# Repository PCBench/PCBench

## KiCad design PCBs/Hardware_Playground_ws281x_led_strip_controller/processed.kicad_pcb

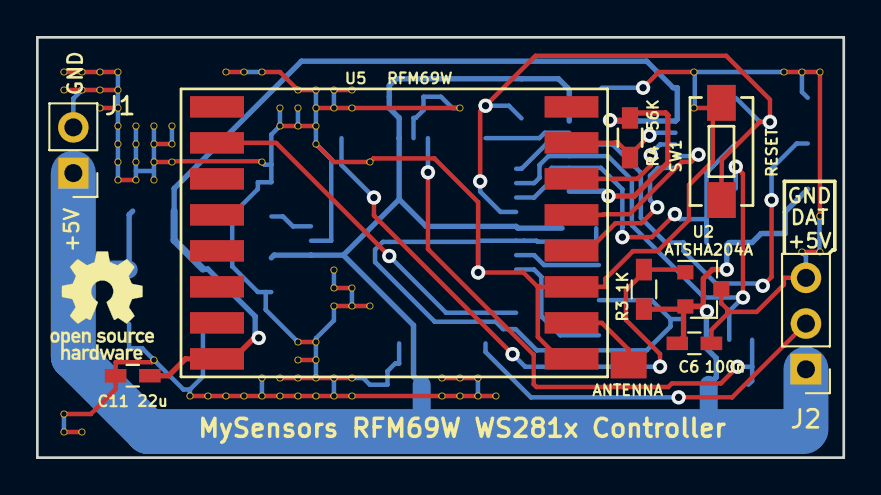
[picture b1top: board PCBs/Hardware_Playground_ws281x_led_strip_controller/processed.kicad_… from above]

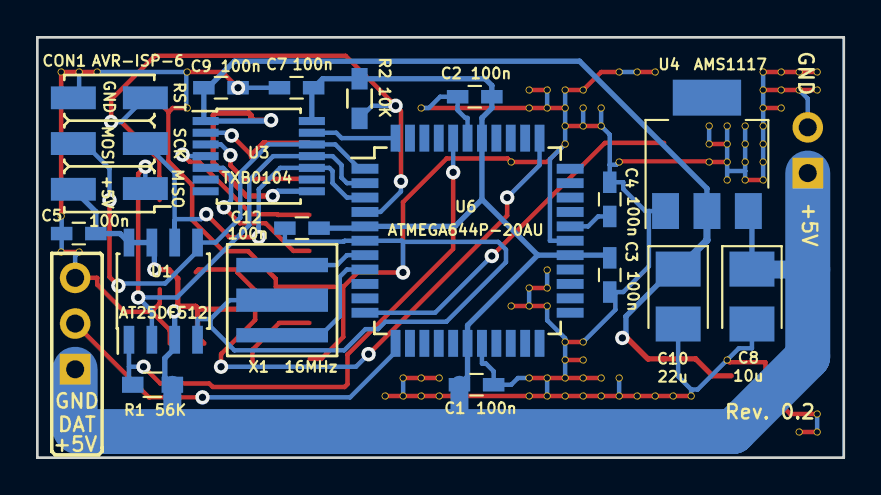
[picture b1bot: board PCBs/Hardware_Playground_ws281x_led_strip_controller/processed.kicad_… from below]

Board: 2 copper layers, 44.8 x 23.4 mm, 117 parts (18 on the bottom side), 20 nets.

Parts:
C1, C2, C3, C4, C5, C6, C7, C9, C12: 100n; C_0603_HandSoldering
C8: 10u; CP_Tantalum_Case-B_EIA-3528-21_Reflow
C10: 22u; CP_Tantalum_Case-B_EIA-3528-21_Reflow
C11: 22u; C_0603_HandSoldering
CON1: AVR-ISP-6; AVR_ISP_SMT_Small_02x03
J1: PWR; Pin_Header_Straight_1x02_Pitch2.54mm
J2: CTRL_OUT; Pin_Header_Straight_1x03_Pitch2.54mm
P1: ANTENNA; 1pin_smd_2mm
R1, R4: 56K; R_0603_HandSoldering
R2: 10K; R_0603_HandSoldering
R3: 1K; R_0603_HandSoldering
SW1: RESET; SW_SPST_EVQPE1
U1: AT25DF512; SOIC-8_3.9x4.9mm_Pitch1.27mm
U2: ATSHA204A; SOT-23
U3: TXB0104; TSSOP-14_4.4x5mm_Pitch0.65mm
U4: AMS1117; SOT-223
U5: RFM69W; RFM69HW_SMD_Handsoldering
U6: ATMEGA644P-20AU; TQFP-44_10x10mm_Pitch0.8mm
V10_2, V10_3, V10_21, V10_22, V11_2, V11_3, V11_22, V12_2, V12_3, V12_4, V13_2, V13_3, V13_4, V13_5, V13_6, V13_7, V13_8, V14_5, V14_6, V14_7, V14_8, V15_5, V15_6, V15_7, V15_8, V15_18, V16_5, V16_6, V16_7, V17_20, V18_20, V19_2, V19_20, V20_2, V20_20, V21_2, V21_7, V21_19, V21_20, V22_4, V22_5, V22_19, V22_20, V23_3, V23_4, V23_5, V23_17, V23_18, V23_19, V23_20, V24_3, V24_4, V24_5, V24_6, V24_17, V24_18, V24_19, V24_20, V25_3, V25_4, V25_13, V25_14, V25_15, V25_19, V25_20, V26_3, V26_4, V26_14, V26_15, V26_19, V26_20, V27_7, V27_15, V31_19, V31_20, V32_4, V32_19, V32_20, V33_19, V33_20, V34_20, V45_2, V45_4, V50_2, V51_2, V51_12, V52_2, V52_10, V52_12: AUTO_VIA; VIA_MATRIX
X1: 16MHz; ZTTCS-3

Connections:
+3V3: C9.2, C10.1, C11.1, R4.2, U3.1, U3.8, U4.2, U5.8
+5V: C1.2, C2.2, C3.2, C5.1, C6.1, C7.1, C8.1, C12.2, CON1.2, J1.1, J2.1, R1.2, R2.1, R3.2, U1.3, U1.7, U1.8, U2.2, U3.14, U4.3, U6.5, U6.17, U6.27, U6.38
/ATSHA204A: R3.1, U2.1, U6.34
/D_OUT: J2.2, U6.12
/MISO: CON1.1, U1.2, U3.11, U6.2
/MOSI: CON1.4, U1.5, U3.12, U6.1
/RFM69W_INT: U5.2, U6.11
/RFM69W_SS: U3.13, U6.44
/RST: CON1.5, R2.2, SW1.1, U6.4
/SCK: CON1.3, U1.6, U3.10, U6.3
/SPI_FLASH_SS: R1.1, U1.1, U6.40
GND: C1.1, C2.1, C3.1, C4.1, C5.2, C6.2, C7.2, C8.2, C9.1, C10.2, C11.2, C12.1, CON1.6, J1.2, J2.3, SW1.2, U1.4, U2.3, U4.1, U5.9, U5.11, U6.6, U6.18, U6.28, U6.39, V10_2.1, V10_3.1, V10_21.1, V10_22.1, V11_2.1, V11_3.1, V11_22.1, V12_2.1, V12_3.1, V12_4.1, V13_2.1, V13_3.1, V13_4.1, V13_5.1, V13_6.1, V13_7.1, V13_8.1, V14_5.1, V14_6.1, V14_7.1, V14_8.1, V15_5.1, V15_6.1, V15_7.1, V15_8.1, V15_18.1, V16_5.1, V16_6.1, V16_7.1, V17_20.1, V18_20.1, V19_2.1, V19_20.1, V20_2.1, V20_20.1, V21_2.1, V21_7.1, V21_19.1, V21_20.1, V22_4.1, V22_5.1, V22_19.1, V22_20.1, V23_3.1, V23_4.1, V23_5.1, V23_17.1, V23_18.1, V23_19.1, V23_20.1, V24_3.1, V24_4.1, V24_5.1, V24_6.1, V24_17.1, V24_18.1, V24_19.1, V24_20.1, V25_3.1, V25_4.1, V25_13.1, V25_14.1, V25_15.1, V25_19.1, V25_20.1, V26_3.1, V26_4.1, V26_14.1, V26_15.1, V26_19.1, V26_20.1, V27_7.1, V27_15.1, V31_19.1, V31_20.1, V32_4.1, V32_19.1, V32_20.1, V33_19.1, V33_20.1, V34_20.1, V45_2.1, V45_4.1, V50_2.1, V51_2.1, V51_12.1, V52_2.1, V52_10.1, V52_12.1, X1.2
unnamed: C4.2, U6.29
unnamed: P1.1, U5.10
unnamed: R4.1, U3.2, U5.15
unnamed: U3.3, U5.14
unnamed: U3.4, U5.13
unnamed: U3.5, U5.12
unnamed: U6.7, X1.1
unnamed: U6.8, X1.3

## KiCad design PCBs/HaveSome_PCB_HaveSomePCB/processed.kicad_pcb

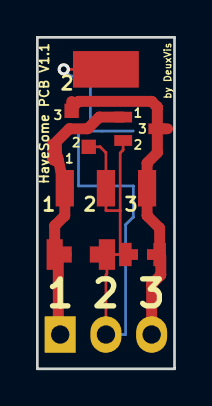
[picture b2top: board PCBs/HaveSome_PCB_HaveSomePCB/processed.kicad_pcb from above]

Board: 2 copper layers, 7.6 x 18.4 mm, 8 parts (0 on the bottom side), 3 nets.

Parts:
PINS1: CONN_01X03; Pin_Header_Straight_1x03
SMD402: R0402; R_0402
SMD603: R0603; R_0603
SMD805: R0805; R_0805
SMD1206: R1206; R_1206
SOT23: APE8865NL-33-HF-3; SOT-23
SOT223: LD1117S33CTR; SOT-223
SOT323: BFR92; SOT-323

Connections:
unnamed: PINS1.1, SMD603.2, SMD1206.2, SOT23.1, SOT223.1, SOT323.1
unnamed: PINS1.2, SMD402.2, SMD603.1, SMD805.2, SMD1206.1, SOT23.2, SOT223.2, SOT223.4, SOT323.2
unnamed: PINS1.3, SMD402.1, SMD805.1, SOT23.3, SOT223.3, SOT323.3

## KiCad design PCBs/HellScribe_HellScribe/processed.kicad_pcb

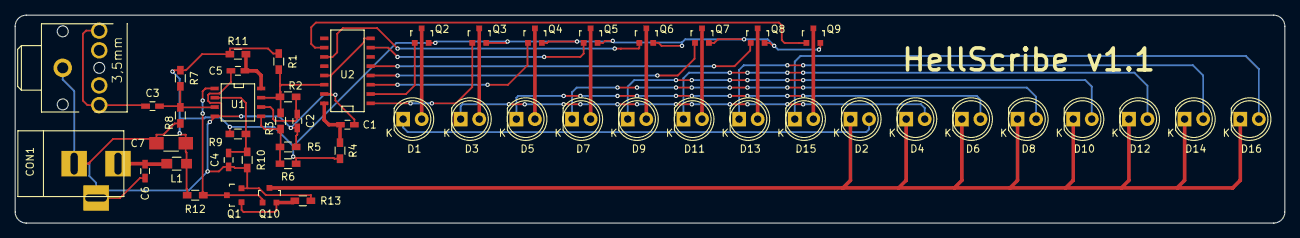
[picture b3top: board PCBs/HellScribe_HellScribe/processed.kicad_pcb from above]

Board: 2 copper layers, 173.7 x 28.4 mm, 51 parts (0 on the bottom side), 38 nets.

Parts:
C1, C3, C4, C5, C6: 0.1uF; C_0603_HandSoldering
C2: 2.2nF; C_0603_HandSoldering
C7: 10uF; R_1206_HandSoldering
CON1: +12v; BARREL_JACK
D1, D2, D3, D4, D5, D6, D7, D8, D9, D10, D11, D12, D13, D14, D15, D16: LED; LED-5MM
J1: STX-3100-5N; STX3100
L1: 10uH; R_0805_HandSoldering
Q1, Q10: 2N3904; SOT-23
Q2, Q3, Q4, Q5, Q6, Q7, Q8, Q9: FDV304P; SOT-23
R1: 1k; R_0603_HandSoldering
R2: 2.4M; R_0603_HandSoldering
R3, R5, R6, R7, R8, R9: 10k; R_0603_HandSoldering
R4, R11: 100; R_0603_HandSoldering
R10: 11k; R_0603_HandSoldering
R12: 2.2k; R_0603_HandSoldering
R13: 10; R_0603_HandSoldering
U1: LM393; SOIC-8-N
U2: CD4022; SO-16-N

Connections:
+12V: C7.2, L1.1, Q2.2, Q3.2, Q4.2, Q5.2, Q6.2, Q7.2, Q8.2, Q9.2, R1.1, R4.1, R6.2, R7.1, R9.2, R11.1, R12.2
GND: C1.2, C2.1, C4.1, C5.1, C6.1, C7.1, CON1.2, CON1.3, J1.1, Q1.2, R5.1, R8.2, R10.2, R13.2, U1.4, U2.8, U2.13, U2.15
unnamed: C2.2, R2.2, U1.6
unnamed: C3.1, R7.2, R8.1, U1.3
unnamed: C3.2, J1.2, J1.5
unnamed: C4.2, R9.1, R10.1, U1.2
unnamed: C5.2, R11.2, U1.8
unnamed: C6.2, CON1.1, L1.2
unnamed: D1.1, D2.2
unnamed: D1.2, Q2.3
unnamed: D3.1, D4.2
unnamed: D3.2, Q3.3
unnamed: D5.1, D6.2
unnamed: D5.2, Q4.3
unnamed: D7.1, D8.2
unnamed: D7.2, Q5.3
unnamed: D9.2, Q6.3
unnamed: D2.1, D4.1, D6.1, D8.1, D10.1, D12.1, D14.1, D16.1, Q10.3
unnamed: D9.1, D10.2
unnamed: D11.1, D12.2
unnamed: D11.2, Q7.3
unnamed: D13.1, D14.2
unnamed: D13.2, Q8.3
unnamed: D15.1, D16.2
unnamed: D15.2, Q9.3
unnamed: Q1.1, Q10.2, R13.1
unnamed: Q1.3, Q10.1, R12.1, U1.1
unnamed: Q2.1, U2.2
unnamed: Q3.1, U2.1
unnamed: Q4.1, U2.3
unnamed: Q5.1, U2.7
unnamed: Q6.1, U2.11
unnamed: Q7.1, U2.4
unnamed: Q8.1, U2.5
unnamed: Q9.1, U2.10
unnamed: R1.2, R2.1, R3.2, U1.7, U2.14
unnamed: R3.1, R5.2, R6.1, U1.5
VDD: C1.1, R4.2, U2.16

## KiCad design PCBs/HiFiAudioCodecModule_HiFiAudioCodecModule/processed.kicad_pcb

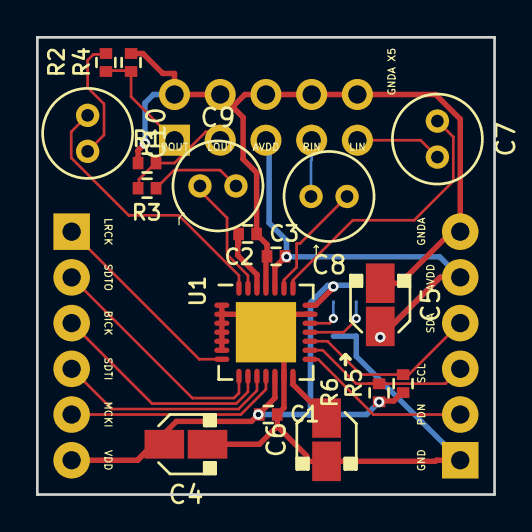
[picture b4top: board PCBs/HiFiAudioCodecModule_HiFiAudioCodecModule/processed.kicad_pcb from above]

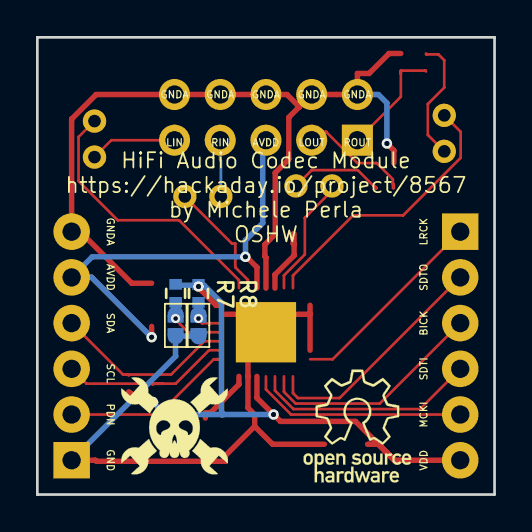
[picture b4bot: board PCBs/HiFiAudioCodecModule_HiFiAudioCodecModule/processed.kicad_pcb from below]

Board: 2 copper layers, 25.4 x 25.4 mm, 26 parts (6 on the bottom side), 26 nets.

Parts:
C1, C2: 0.1u; C_0402
C3: 1u; C_0402
C4, C5: 10u; CAP_ELEC_SMD_3x5mm
C6: 1u; CAP_ELEC_SMD_3x5mm
C7, C8: 10u; C_Radial_D5_L11_P2-bipolar
C9, C10: 1u; C_Radial_D5_L11_P2-bipolar
JP1, JP2: Jumper_NO_Small; SMD_Jumper
LOGO1: OSHW; LOGO
LOGO2: HACKADAY; LOGO
P1, P2: CONN_01X06; Pin_Header_Straight_1x06
P3: CONN_02X05; Pin_Header_Straight_2x05
R1, R2: 220; R_0402
R3, R4: 20K; R_0402
R5, R6, R7, R8: 1K; R_0402
U1: AK4558EN; QFN-28-2xEP_5x5mm_Pitch0.5mm

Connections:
AVDD: C2.1, C5.1, P2.5, P3.5, U1.24
BICK: P1.3, U1.9
CAD0: JP1.1, R7.2, U1.18
CAD1: JP2.1, R8.2, U1.19
GND: C1.2, C4.2, C6.2, JP1.2, JP2.2, P2.1, U1.1, U1.2, U1.3, U1.4, U1.5, U1.6, U1.13, U1.20, U1.29
GNDA: C2.2, C3.2, C5.2, P2.6, P3.2, P3.4, P3.6, P3.8, P3.10, R3.2, R4.2, U1.25
LIN: C7.1, U1.22
LIN-CON: C7.2, P3.9
LOUT: C9.1, U1.27
LOUT-CON: P3.3, R1.1, R3.1
LRCK: P1.1, U1.7
MCKI: P1.5, U1.11
unnamed: C9.2, R1.2
unnamed: C10.2, R2.2
PDN: P2.2, U1.15
RIN: C8.1, U1.23
RIN-CON: C8.2, P3.7
ROUT: C10.1, U1.28
ROUT-CON: P3.1, R2.1, R4.1
SCL: P2.3, R6.2, U1.16
SDA: P2.4, R5.2, U1.17
SDTI: P1.4, U1.10
SDTO: P1.2, U1.8
VCOM: C3.1, U1.26
VDD: C1.1, C4.1, P1.6, R5.1, R6.1, R7.1, R8.1, U1.12, U1.21
VDD18: C6.1, U1.14

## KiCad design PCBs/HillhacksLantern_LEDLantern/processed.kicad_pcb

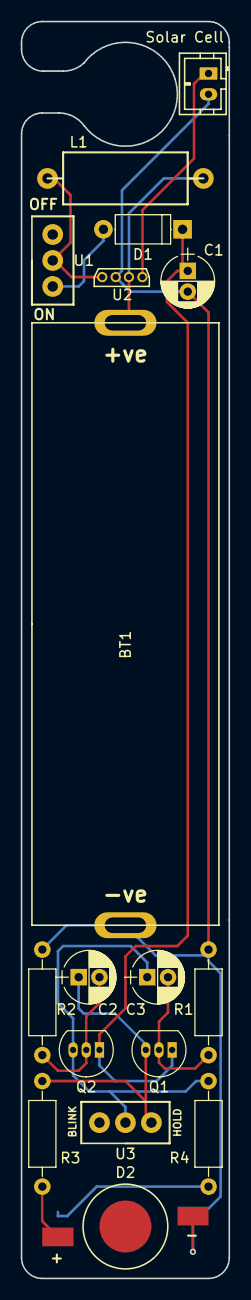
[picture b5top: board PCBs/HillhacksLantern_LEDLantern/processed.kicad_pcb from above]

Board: 2 copper layers, 20.0 x 121.0 mm, 18 parts (1 on the bottom side), 12 nets.

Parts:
BT1: Battery_Cell; BatteryHolder
C1, C2, C3: CP; CP_Radial_D5.0mm_P2.00mm
D1: D; D_A-405_P7.62mm_Horizontal
D2, D3: LED; 1W-LED
L1: L; Inductor
Q1, Q2: Q_PNP_EBC; TO-92_Inline_Narrow_Oval
R1, R2, R3, R4: R; R_Axial_DIN0207_L6.3mm_D2.5mm_P10.16mm_Horizontal
Solar Cell: Solar_Cell; JST_PH_B2B-PH-K_02x2.00mm_Straight
U1, U3: switch_on_off; Switch
U2: qf5252; YX8018

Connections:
/GND: BT1.2, C1.2, D2.1, D3.1, R1.2, R2.2, Solar Cell.2, U2.3
/VCC: C1.1, D1.1, Q1.1, Q2.1
unnamed: BT1.1, L1.2, U2.2
unnamed: C2.1, Q1.3, R3.1, U3.1
unnamed: C2.2, Q2.2, R2.1
unnamed: C3.1, Q2.3, R4.1, U3.2
unnamed: C3.2, Q1.2, R1.1
unnamed: D1.2, U1.1
unnamed: D2.2, R3.2
unnamed: D3.2, R4.2
unnamed: L1.1, U1.2, U2.4
unnamed: Solar Cell.1, U2.1

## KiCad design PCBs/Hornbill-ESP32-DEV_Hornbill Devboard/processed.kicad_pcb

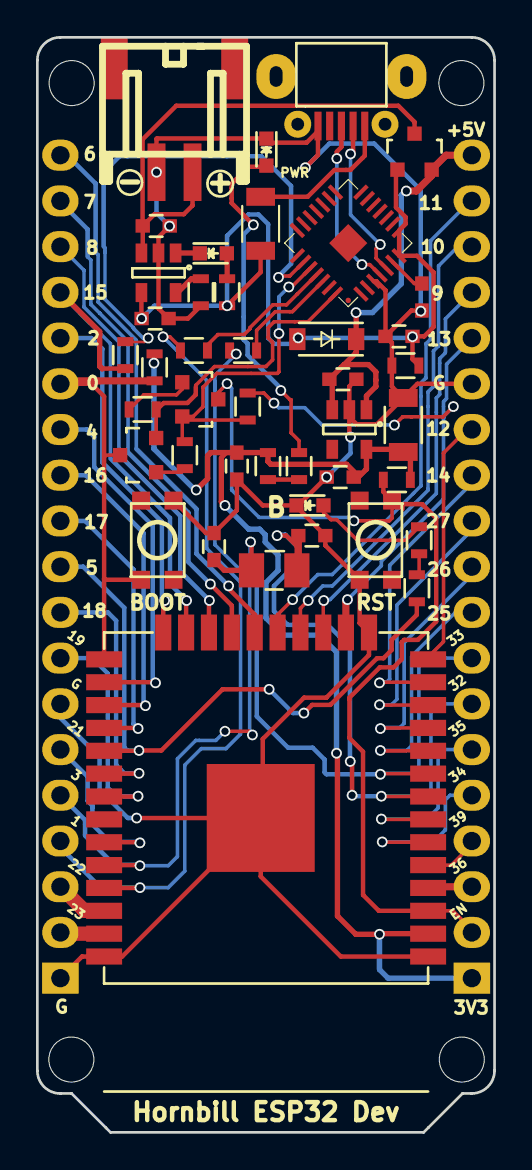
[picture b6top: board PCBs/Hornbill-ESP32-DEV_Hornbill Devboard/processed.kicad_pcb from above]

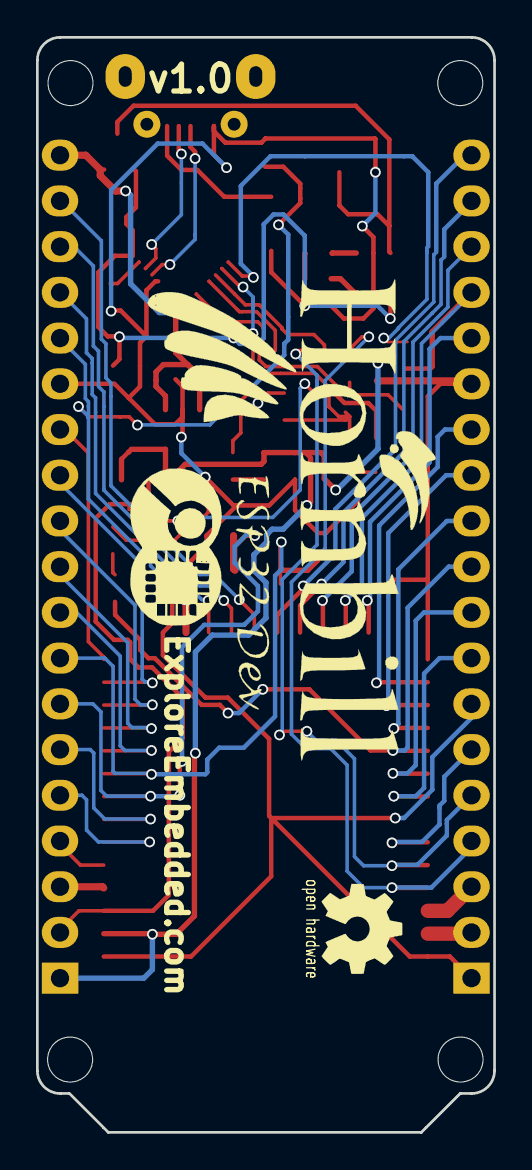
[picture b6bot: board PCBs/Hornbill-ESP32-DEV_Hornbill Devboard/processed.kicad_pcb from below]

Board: 2 copper layers, 25.4 x 60.8 mm, 51 parts (3 on the bottom side), 56 nets.

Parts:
C1, C6: 4.7uF; C_0603
C2: 1uF; C_0603
C3, C4: 0.1uF; C_0603
C5: 2.2uF; C_0603
C7: 100uF; C_1206
C8, C10: 15pF; C_0603
C9: 100nF; C_0603
CON1: USB-MINI-B; USB_Micro-B_SMD_NEW_1
D1: BAT20J; SOD-80_diode
D2: Yellow; LED-0603
D3: LED; LED-0603
D4: Blue; LED-0603
F1: 500mA; Fuse_500mA
IC1: MCP73831; SOT-23-5
M1: ESP-WROOM-32; ESP-32S
P1: LIPO; JST_SMD
P2, P3: CONN_01X19; Pin_Header_Straight_1x19
Q1: IRLML5203; SOT-23
Q2, Q3: S8050; SOT-23
R1: 100K; R_0603
R2: 2K; R_0603
R3, R4: 1K; R_0603
R5, R6: 12K; R_0603
R7, R11: 10K; R_0603
R8, R9, R10, R12, R16, R17: 0E; R_0603
R13: 330E; R_0603
SW1, SW2: SW_PUSH; smd_push2_New
U1: OSH_Symbol; Logo_silk_OSHW_6x6mm
U2: EE_Logo; Hornbill_ESP32_Dev
U3: EE_Logo; Logo_8
U4: AP2112K; SOT-23-5
U5: CP2102; cp2102_xl2
U6, U7, U8, U9: MountingHole; MountingHole_2-5mm
Y1: 32.768KHz RTC Crystal; SMD_RTC_Crstl

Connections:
+3V3: C5.1, C7.1, C9.1, M1.2, P2.1, R7.1, R11.1, R17.2, U4.5
+5V: C2.1, D1.1, P2.19, Q1.2, U4.1, U4.3
+BATT: C1.1, IC1.3, P1.1, Q1.3
/CLK: M1.20, P3.19
/CMD: M1.19, P2.18
/DTR: Q3.2, R5.2, U5.28
/EN: M1.3, P2.2, Q2.3, R7.2, SW1.1
/IO0: M1.25, P3.14, Q3.3, R11.2, SW2.1
/IO2: M1.24, P3.15
/IO4: M1.26, P3.13
/IO5: M1.29, P3.10, R16.1
/IO12: M1.14, P2.13
/IO13: M1.16, P2.15, R10.1
/IO14: M1.13, P2.12
/IO15: M1.23, P3.16, R12.1
/IO16: M1.27, P3.12
/IO17: M1.28, P3.11
/IO18: M1.30, P3.9
/IO19: M1.31, P3.8
/IO21: M1.33, P3.6
/IO22: M1.36, P3.3
/IO23: M1.37, P3.2
/IO25: M1.10, P2.9
/IO26: M1.11, P2.10
/IO27: M1.12, P2.11
/IO32: C8.1, M1.8, P2.7, Y1.1
/IO33: C10.1, M1.9, P2.8, Y1.2
/IO34: M1.6, P2.5
/IO35: M1.7, P2.6
/RTS: Q2.2, R6.2, R10.2, U5.24
/RXD0: M1.34, P3.5, R8.1
/SD0: M1.21, P3.18
/SD1: M1.22, P3.17
/SD2: M1.17, P2.16
/SD3: M1.18, P2.17
/SENSOR_VN: M1.5, P2.4
/SENSOR_VP: M1.4, P2.3
/TXD0: M1.35, P3.4, R9.1
GND: C1.2, C2.2, C3.1, C4.1, C5.2, C6.2, C7.2, C8.2, C9.2, C10.2, CON1.5, D3.1, D4.1, IC1.2, M1.1, M1.15, M1.38, P1.2, P2.14, P3.1, P3.7, R1.2, R2.2, SW1.2, SW2.2, U4.2, U5.3
unnamed: C4.2, U5.6
unnamed: CON1.1, F1.2
unnamed: CON1.2, U5.5
unnamed: CON1.3, U5.4
unnamed: D2.1, IC1.1
unnamed: D2.2, R4.2
unnamed: D3.2, R3.1
unnamed: D4.2, R13.1
unnamed: IC1.5, R2.1
unnamed: Q2.1, R5.1
unnamed: Q3.1, R6.1
unnamed: R8.2, U5.26
unnamed: R9.2, U5.25
unnamed: R12.2, U5.23
unnamed: R13.2, R16.2
unnamed: R3.2, R17.1
VCC: C3.2, C6.1, D1.2, F1.1, IC1.4, Q1.1, R1.1, R4.1, U5.7, U5.8

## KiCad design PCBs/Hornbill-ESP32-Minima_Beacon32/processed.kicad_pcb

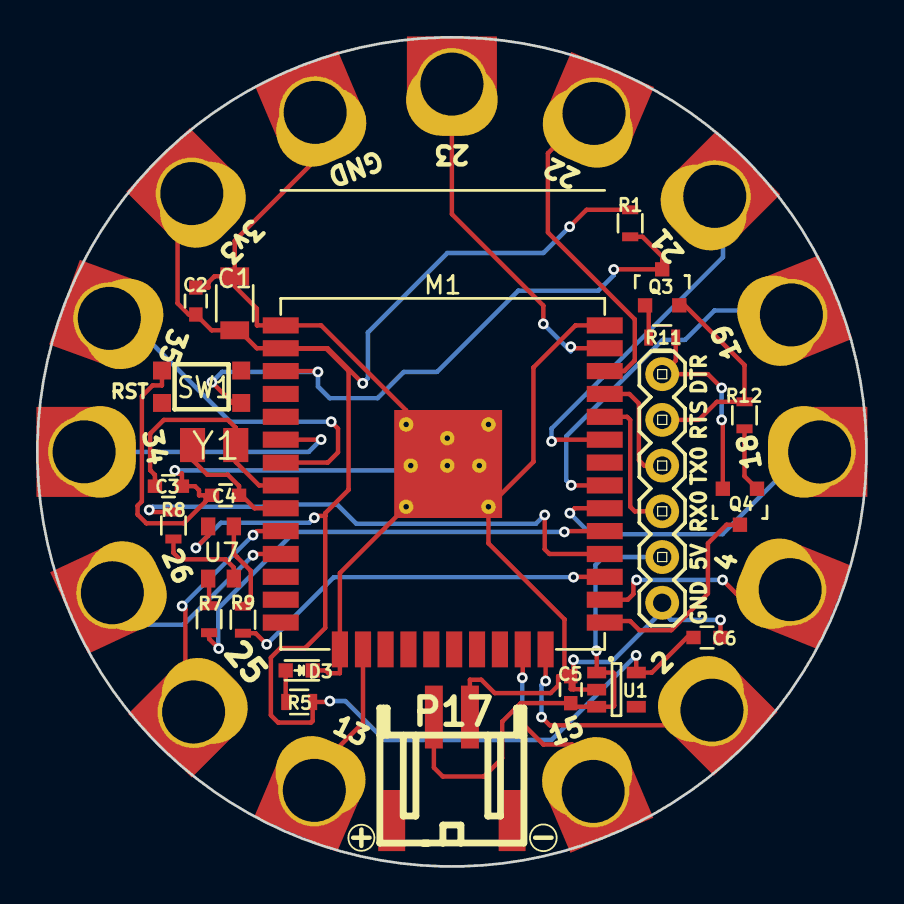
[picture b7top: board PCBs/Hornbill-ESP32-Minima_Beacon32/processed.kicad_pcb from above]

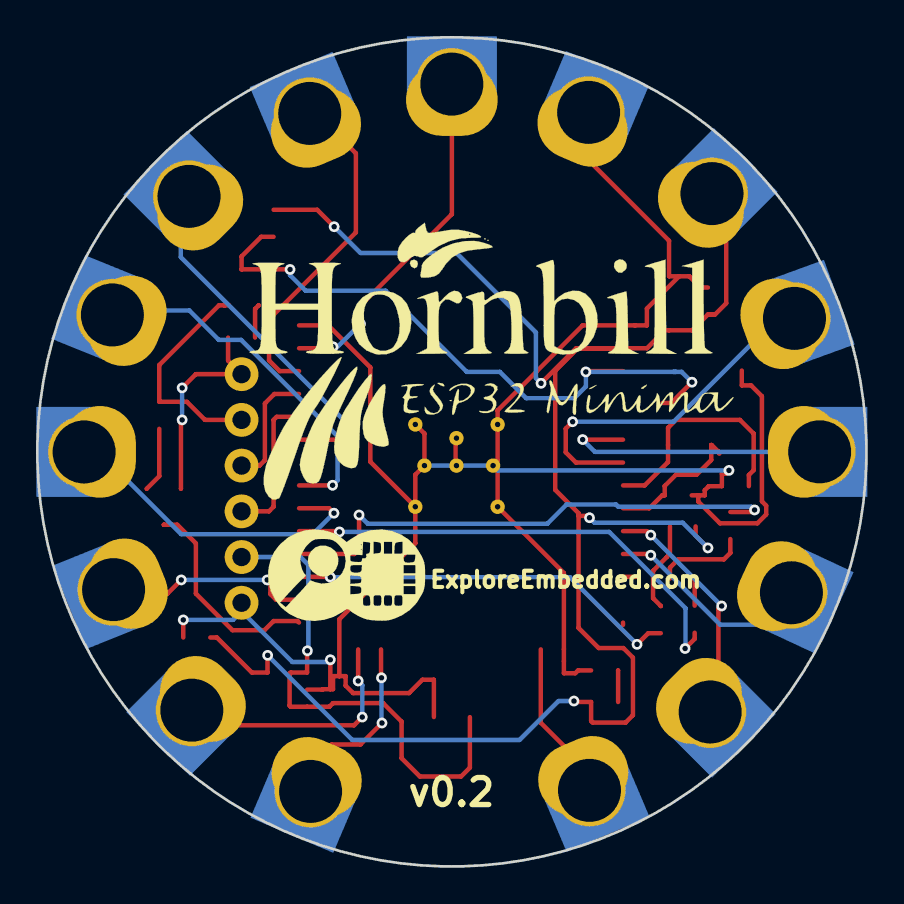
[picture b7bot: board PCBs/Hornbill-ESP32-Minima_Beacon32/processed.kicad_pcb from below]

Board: 2 copper layers, 46.1 x 46.1 mm, 40 parts (2 on the bottom side), 33 nets.

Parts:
C1: 100uF; C_1206
C2: 100nF; C_0603
C3, C4: 15pF; C_0603
C5: 1uF; C_0603
C6: 2.2uF; C_0603
D3: LED; LED-0603
M1: ESP-WROOM-32; ESP-32S
P1, P3, P4, P5, P6, P7, P8, P9, P10, P11, P12, P13, P14, P15, P16: CONN_01X01; MinimaPad_3.5mm
P2: CONN_01X06; 1X06
P17: CONN_01X02; s2b-ph-sm4-tb
Q3, Q4: S8050; SOT-23
R1: 10k; R_0603
R5: 1K; R_0603
R7: 150E; R_0603
R8, R9: 100E; R_0603
R11, R12: 12K; R_0603
SW1: SW_PUSH; smd_push2_New
U1: AP2112K; SOT-23-5
U2: EE_Logo; Hornbill_ESP32_minima
U3: EE_Logo; Logo_8
U7: RGB_4pin; RGB_SMD_4pin_New
Y1: 32.768KHz RTC Crystal; SMD_RTC_Crstl

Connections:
+3V3: C1.1, C2.1, C6.1, M1.2, P1.1, R1.1, R5.2, U1.5, U7.1
+5V: C5.1, P2.2, P17.1, U1.1, U1.3
/2: M1.24, P5.1
/4: M1.26, P11.1
/13: M1.16, P13.1
/15: M1.23, P12.1
/18: M1.30, P8.1
/19: M1.31, P7.1
/21: M1.33, P3.1
/22: M1.36, P4.1
/23: M1.37, P6.1
/25: M1.10, P14.1
/26: M1.11, P15.1
/34: M1.6, P9.1
/35: M1.7, P10.1
/B: M1.27, R9.1
/DTR: P2.6, Q4.2, R11.2
/EN: M1.3, Q3.3, R1.2, SW1.2
/G: M1.28, R8.1
/IO0: M1.25, Q4.3
/R: M1.29, R7.1
/RTS: P2.5, Q3.2, R12.2
/RXD0: M1.34, P2.3
/TXD0: M1.35, P2.4
GND: C1.2, C2.2, C3.2, C4.2, C5.2, C6.2, D3.1, M1.1, M1.15, M1.38, P2.1, P16.1, P17.2, SW1.1, U1.2
unnamed: C3.1, M1.8, Y1.1
unnamed: C4.1, M1.9, Y1.2
unnamed: D3.2, R5.1
unnamed: Q3.1, R11.1
unnamed: Q4.1, R12.1
unnamed: R7.2, U7.2
unnamed: R8.2, U7.4
unnamed: R9.2, U7.3
